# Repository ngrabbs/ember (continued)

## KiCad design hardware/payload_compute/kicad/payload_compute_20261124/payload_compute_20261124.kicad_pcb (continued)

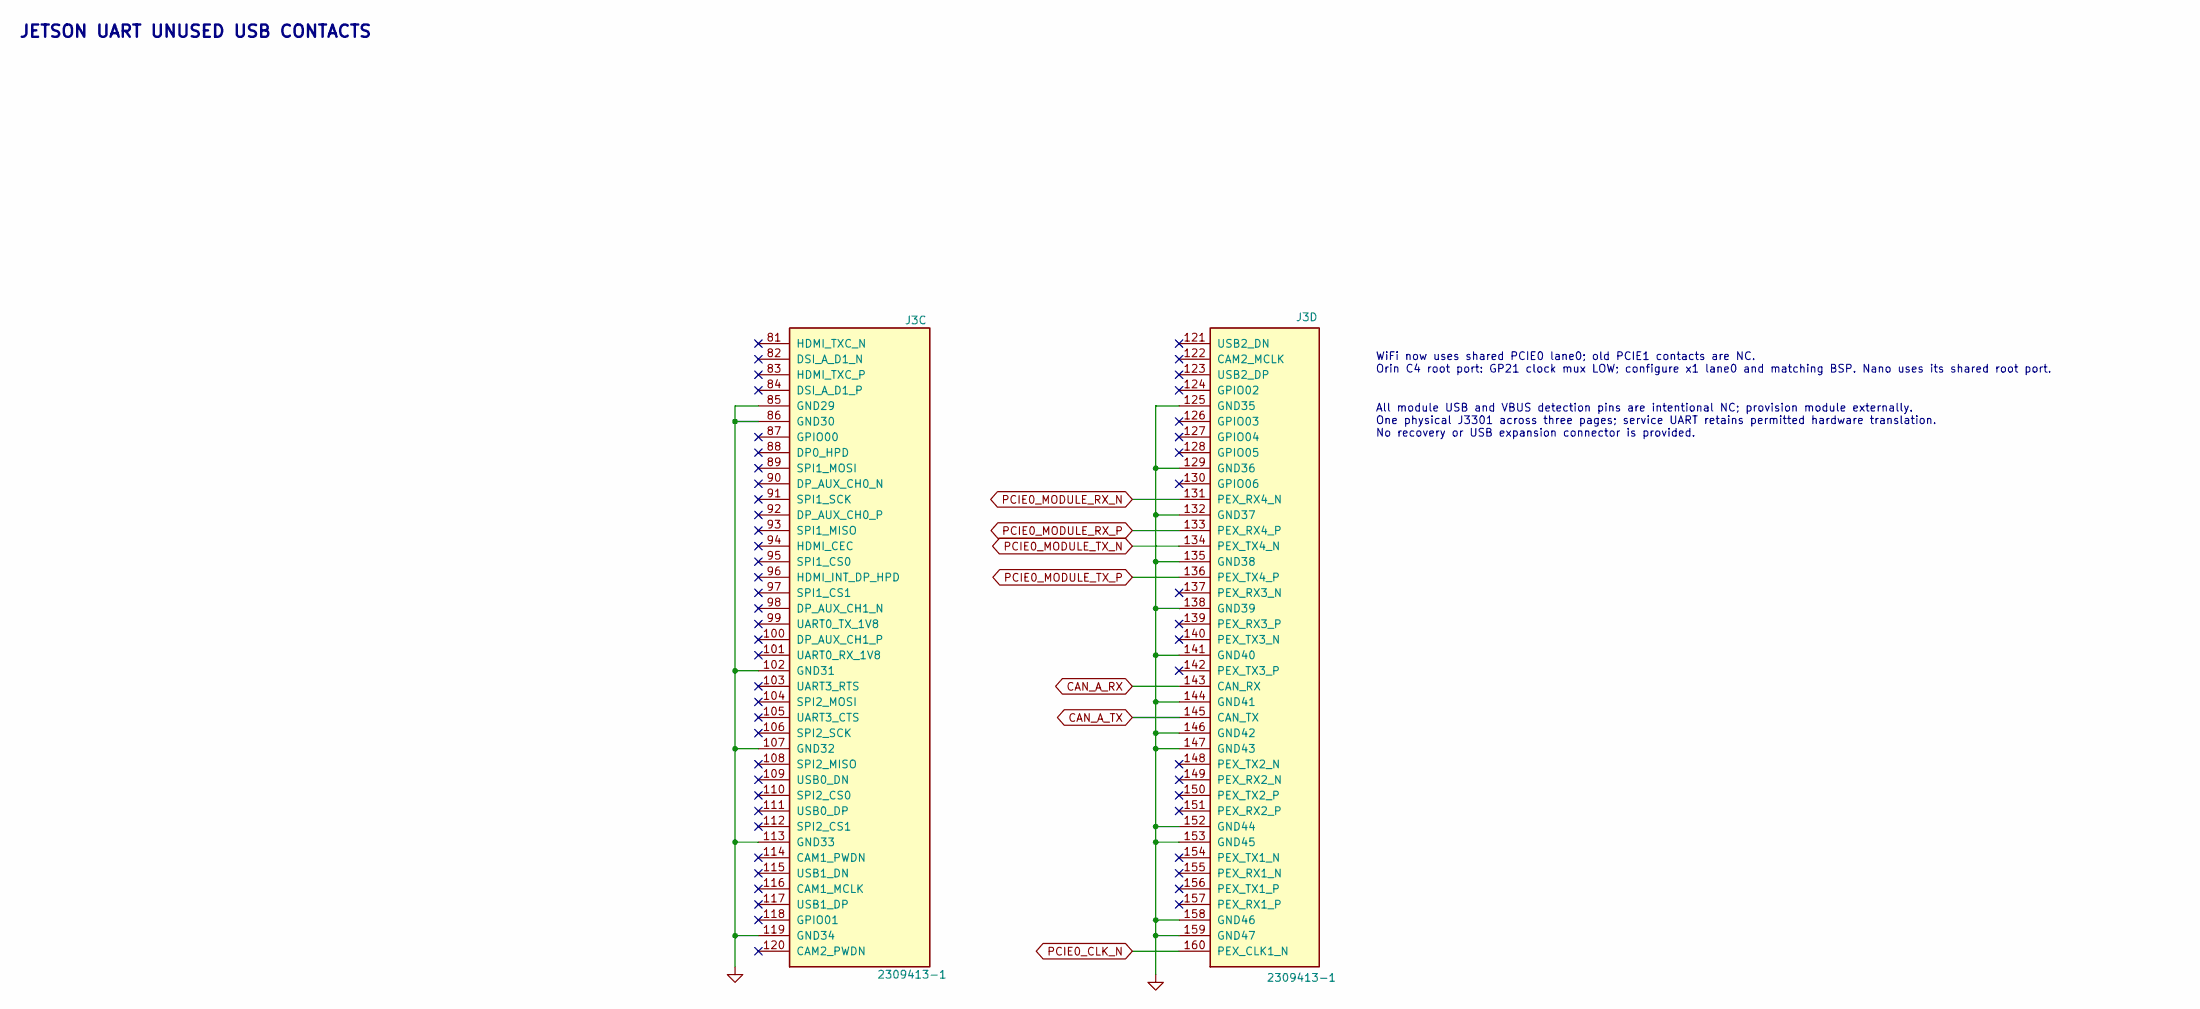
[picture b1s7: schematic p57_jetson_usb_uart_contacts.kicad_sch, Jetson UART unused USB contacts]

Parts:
J3: 2309413-1; TE_2309413_1; MPN 2309413-1

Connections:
CAN_A_RX: J3.143 (CAN_RX); also elsewhere on the board
CAN_A_TX: J3.145 (CAN_TX); also elsewhere on the board
GND: J3.85 (GND29), J3.86 (GND30), J3.102 (GND31), J3.107 (GND32), J3.113 (GND33), J3.119 (GND34), J3.125 (GND35), J3.129 (GND36), J3.132 (GND37), J3.135 (GND38), J3.138 (GND39), J3.141 (GND40), J3.144 (GND41), J3.146 (GND42), J3.147 (GND43), J3.152 (GND44), J3.153 (GND45), J3.158 (GND46), J3.159 (GND47); also elsewhere on the board
PCIE0_CLK_N: J3.160 (PEX_CLK1_N); also elsewhere on the board
PCIE0_MODULE_RX_N: J3.131 (PEX_RX4_N); also elsewhere on the board
PCIE0_MODULE_RX_P: J3.133 (PEX_RX4_P); also elsewhere on the board
PCIE0_MODULE_TX_N: J3.134 (PEX_TX4_N); also elsewhere on the board
PCIE0_MODULE_TX_P: J3.136 (PEX_TX4_P); also elsewhere on the board

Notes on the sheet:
JETSON UART UNUSED USB CONTACTS
All module USB and VBUS detection pins are intentional NC; provision module externally. One physical J3301 across three pages; service UART retains permitted hardware translation. No recovery or USB expansion connector is provided.
WiFi now uses shared PCIE0 lane0; old PCIE1 contacts are NC. Orin C4 root port: GP21 clock mux LOW; configure x1 lane0 and matching BSP. Nano uses its shared root port.

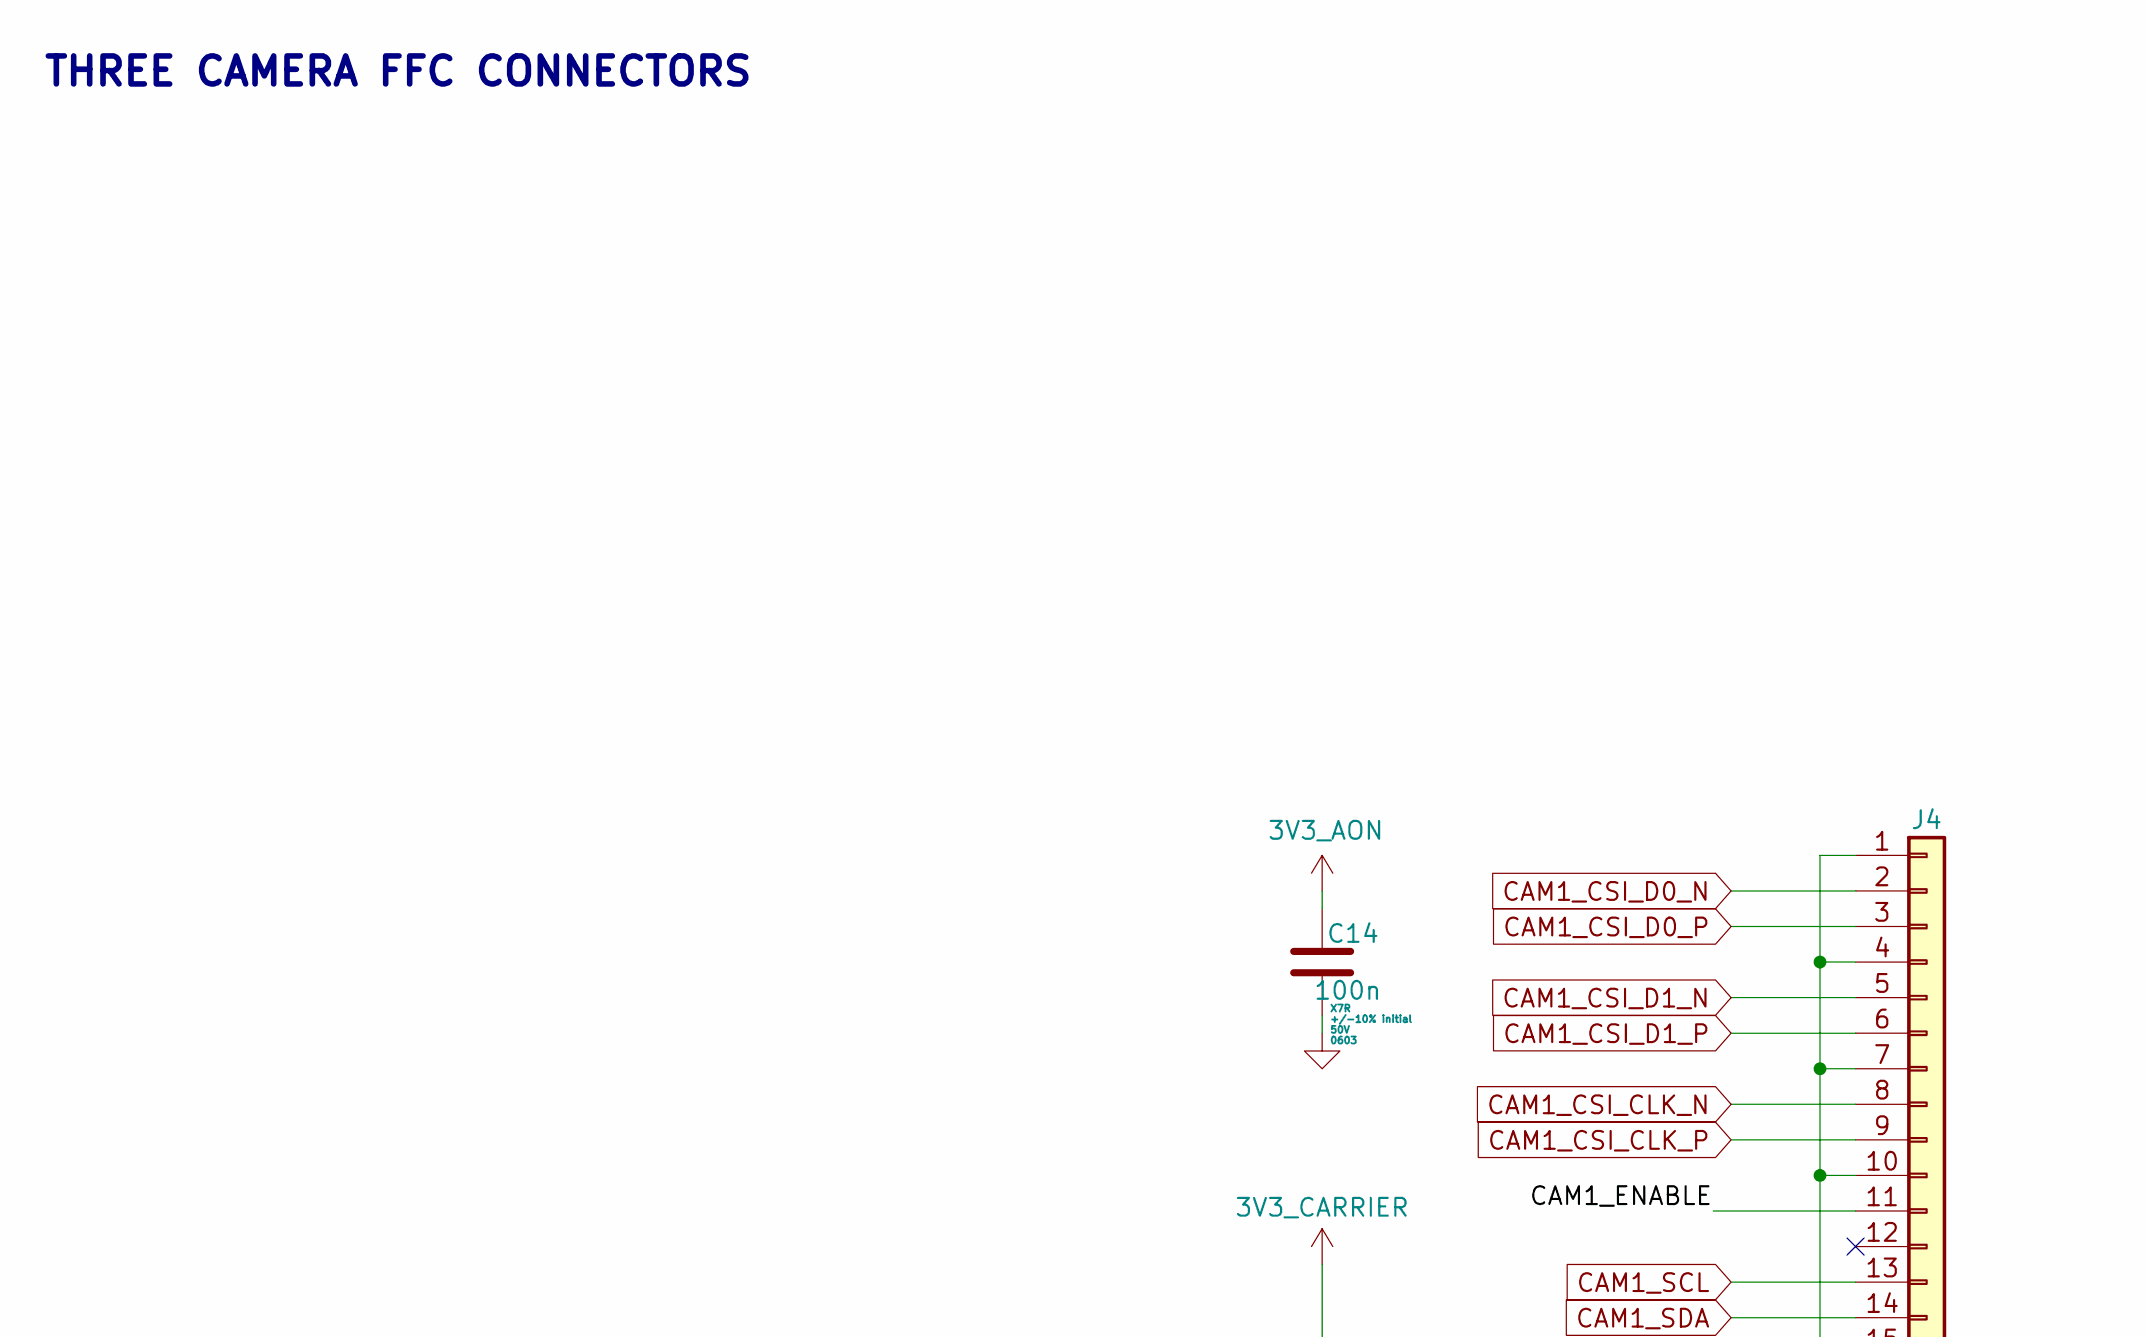
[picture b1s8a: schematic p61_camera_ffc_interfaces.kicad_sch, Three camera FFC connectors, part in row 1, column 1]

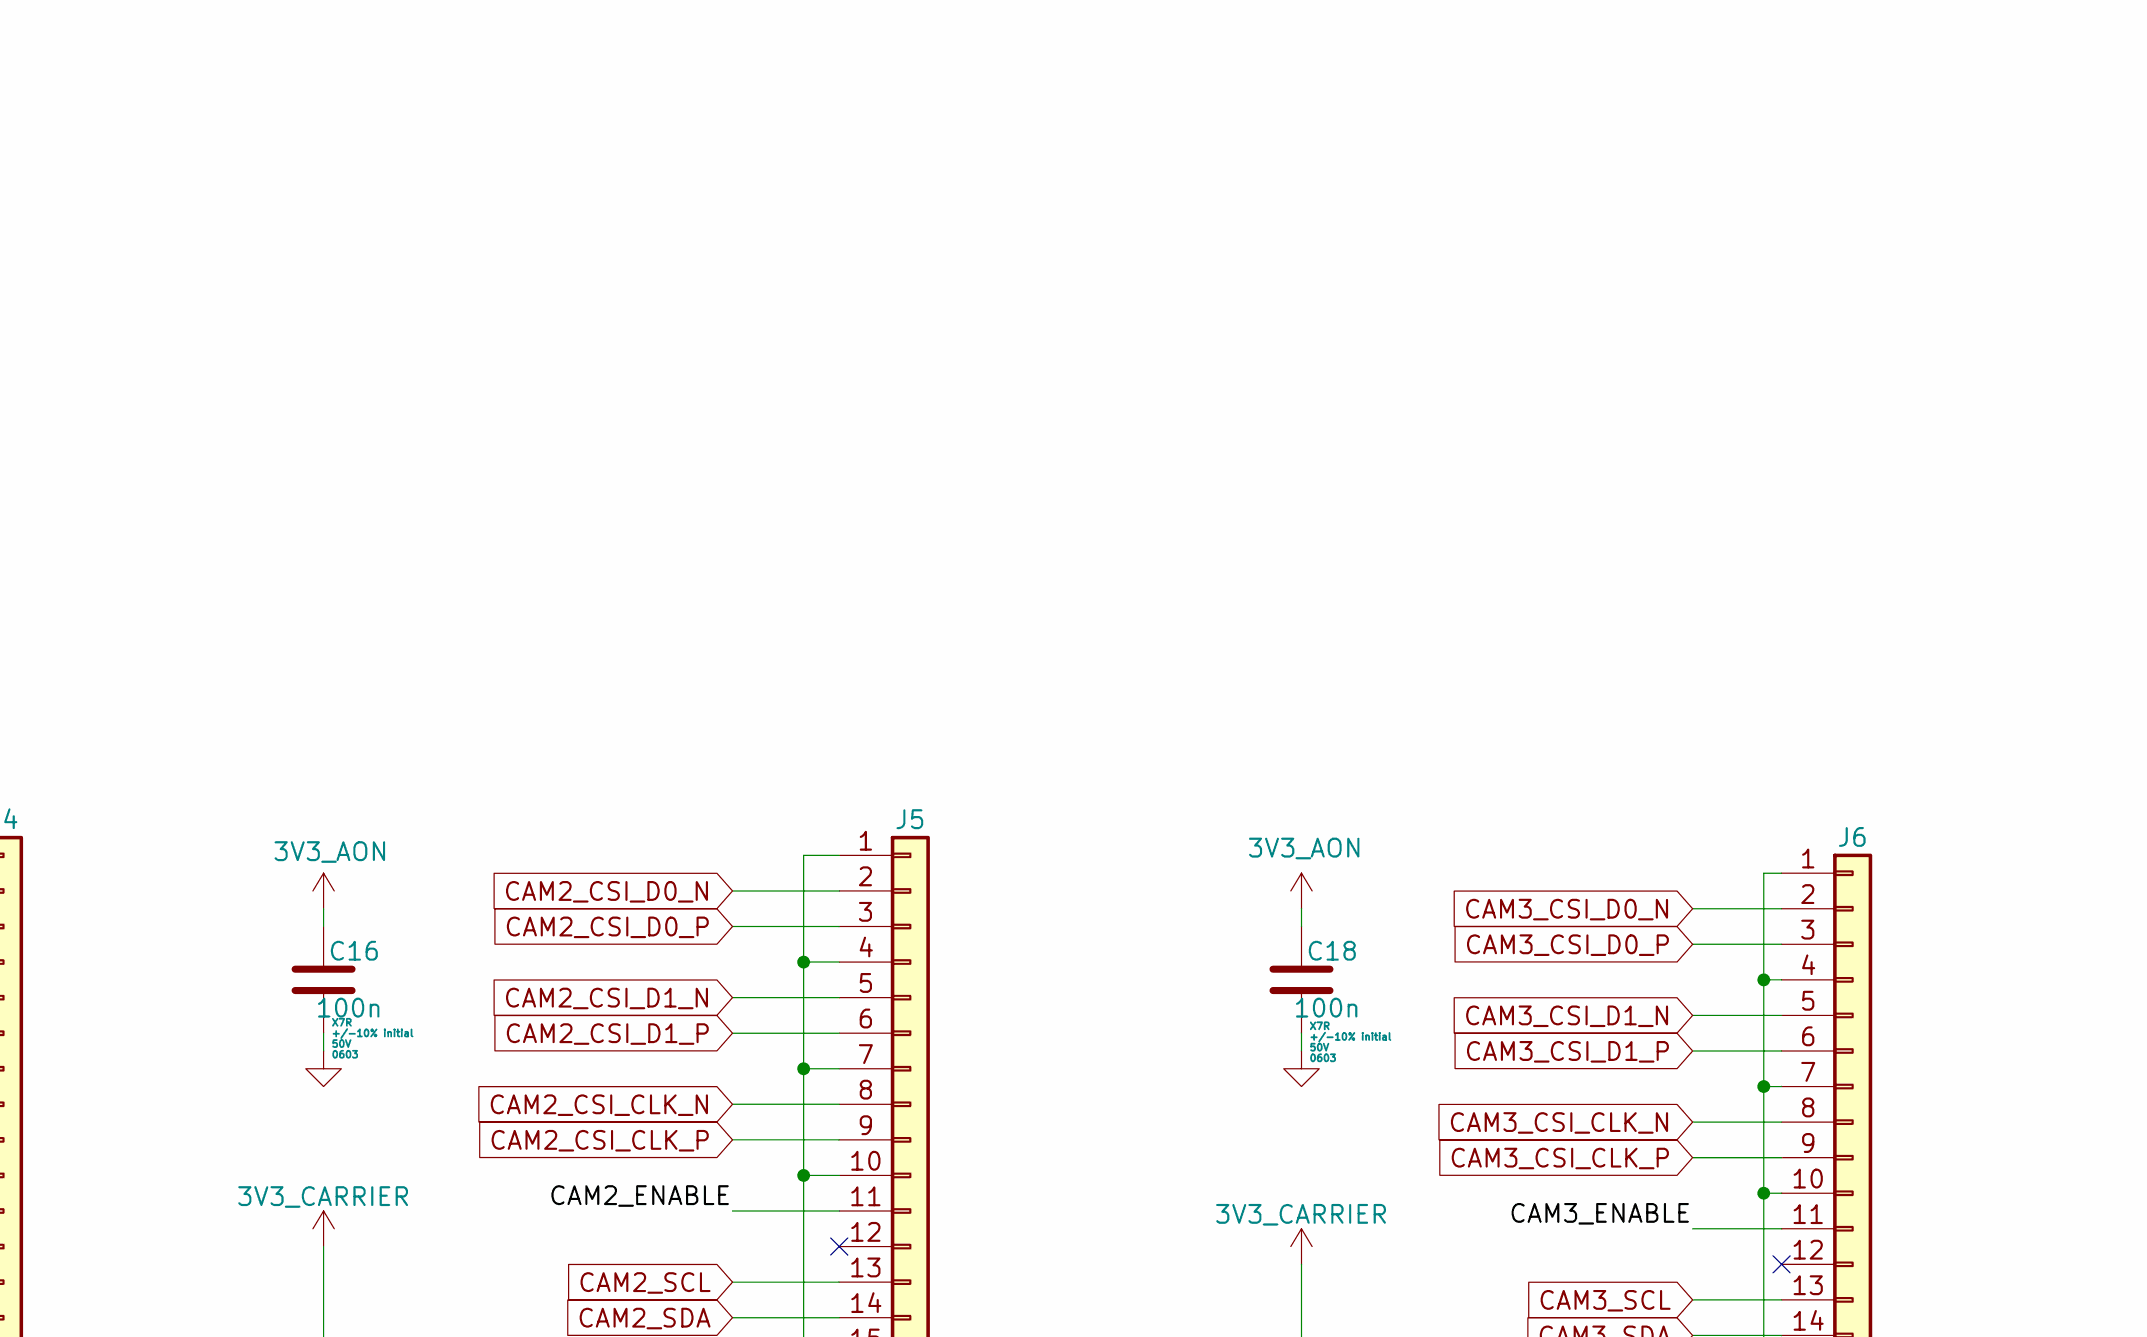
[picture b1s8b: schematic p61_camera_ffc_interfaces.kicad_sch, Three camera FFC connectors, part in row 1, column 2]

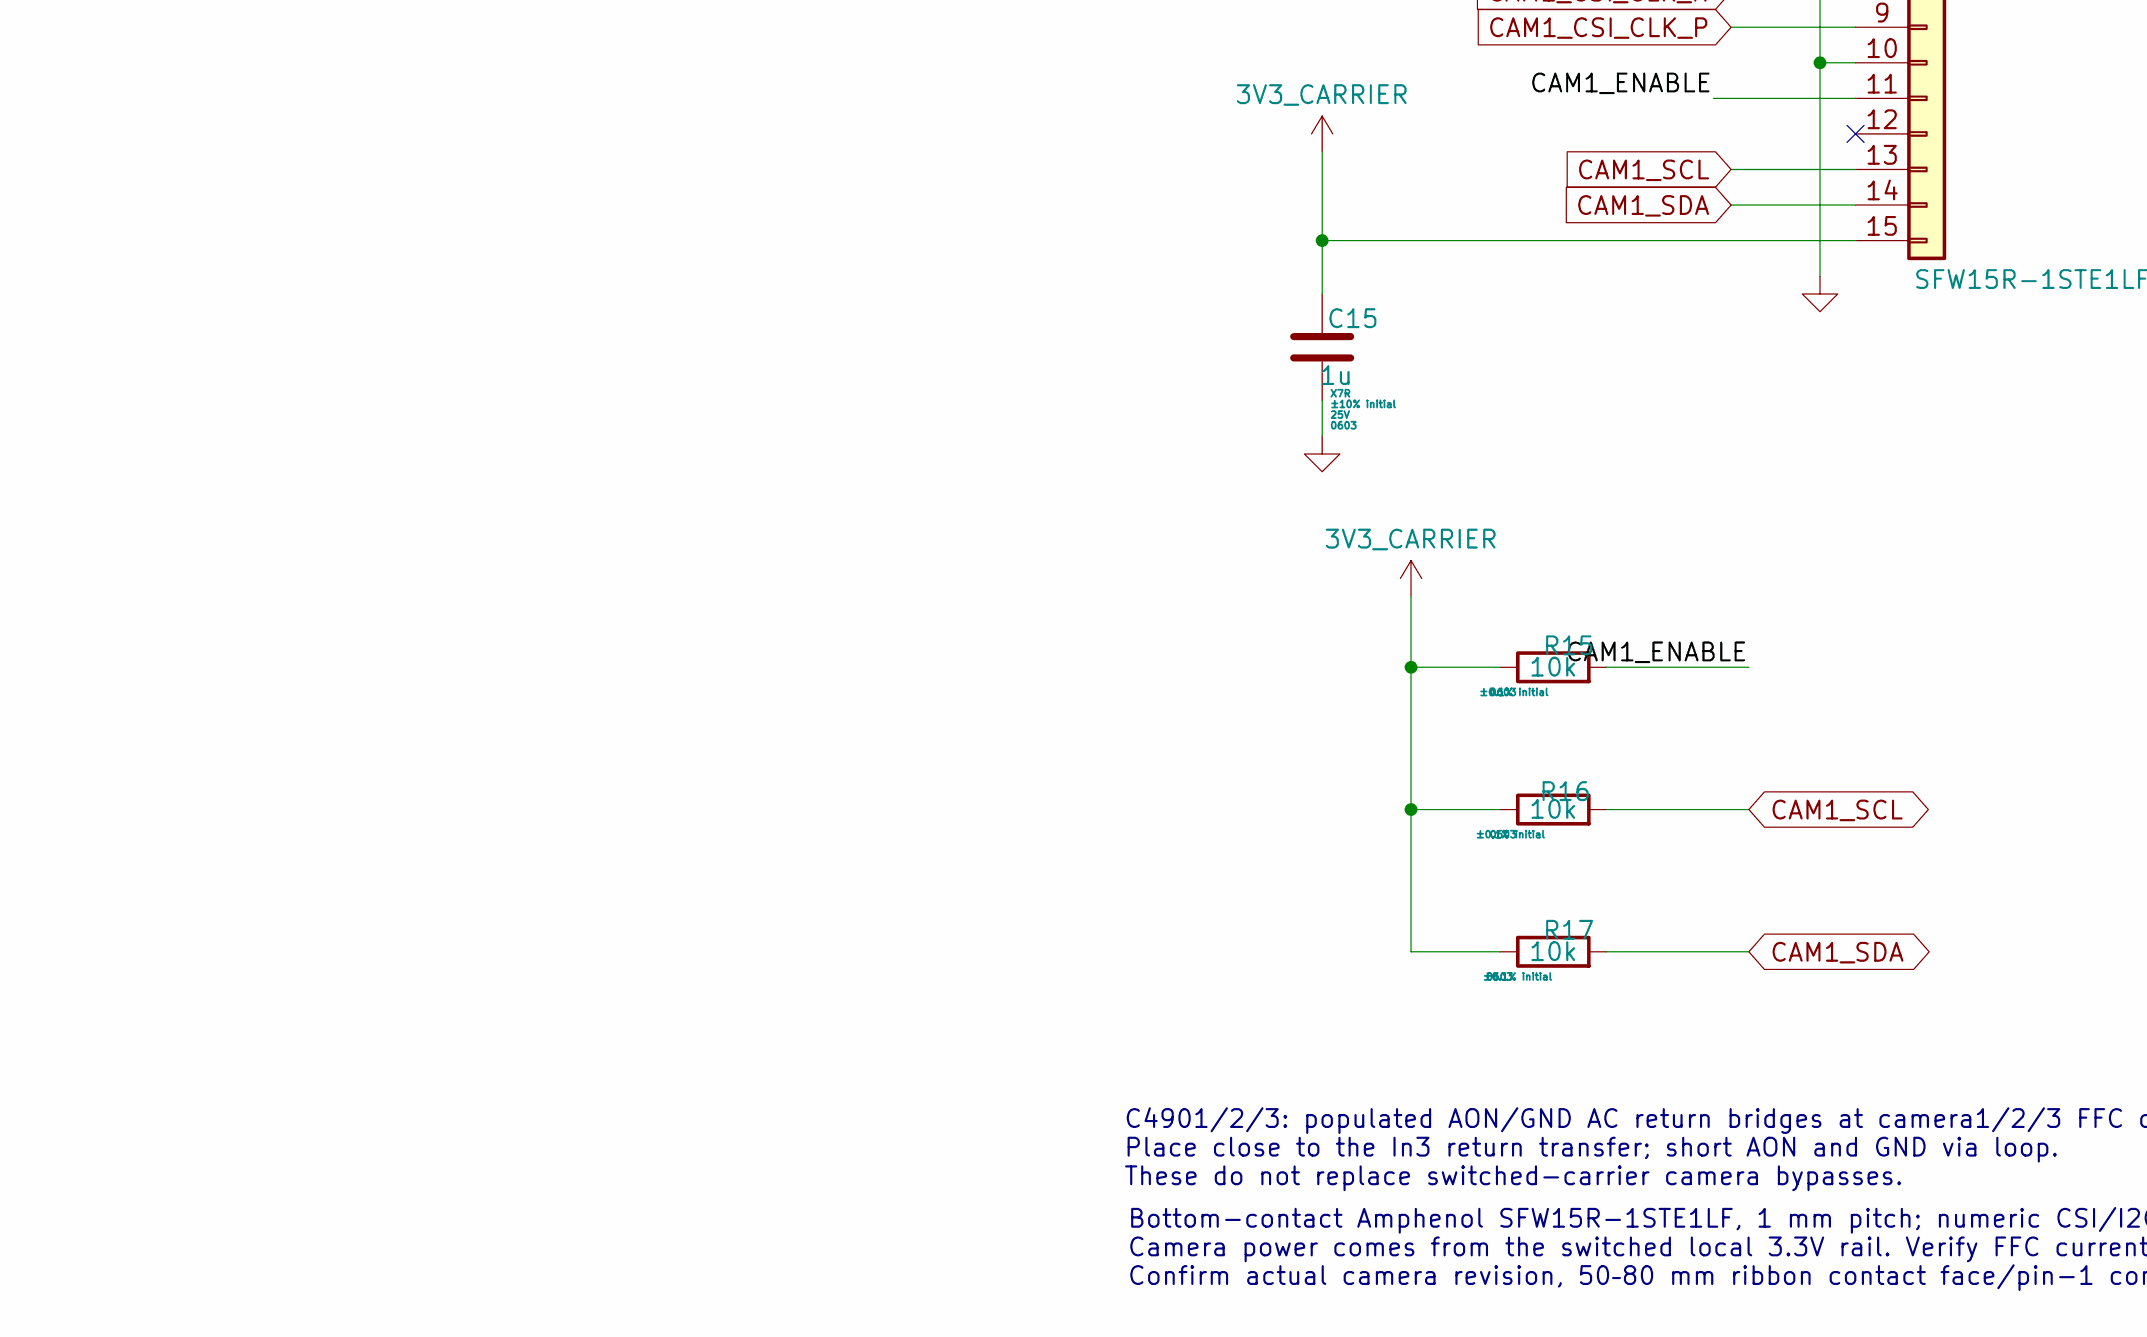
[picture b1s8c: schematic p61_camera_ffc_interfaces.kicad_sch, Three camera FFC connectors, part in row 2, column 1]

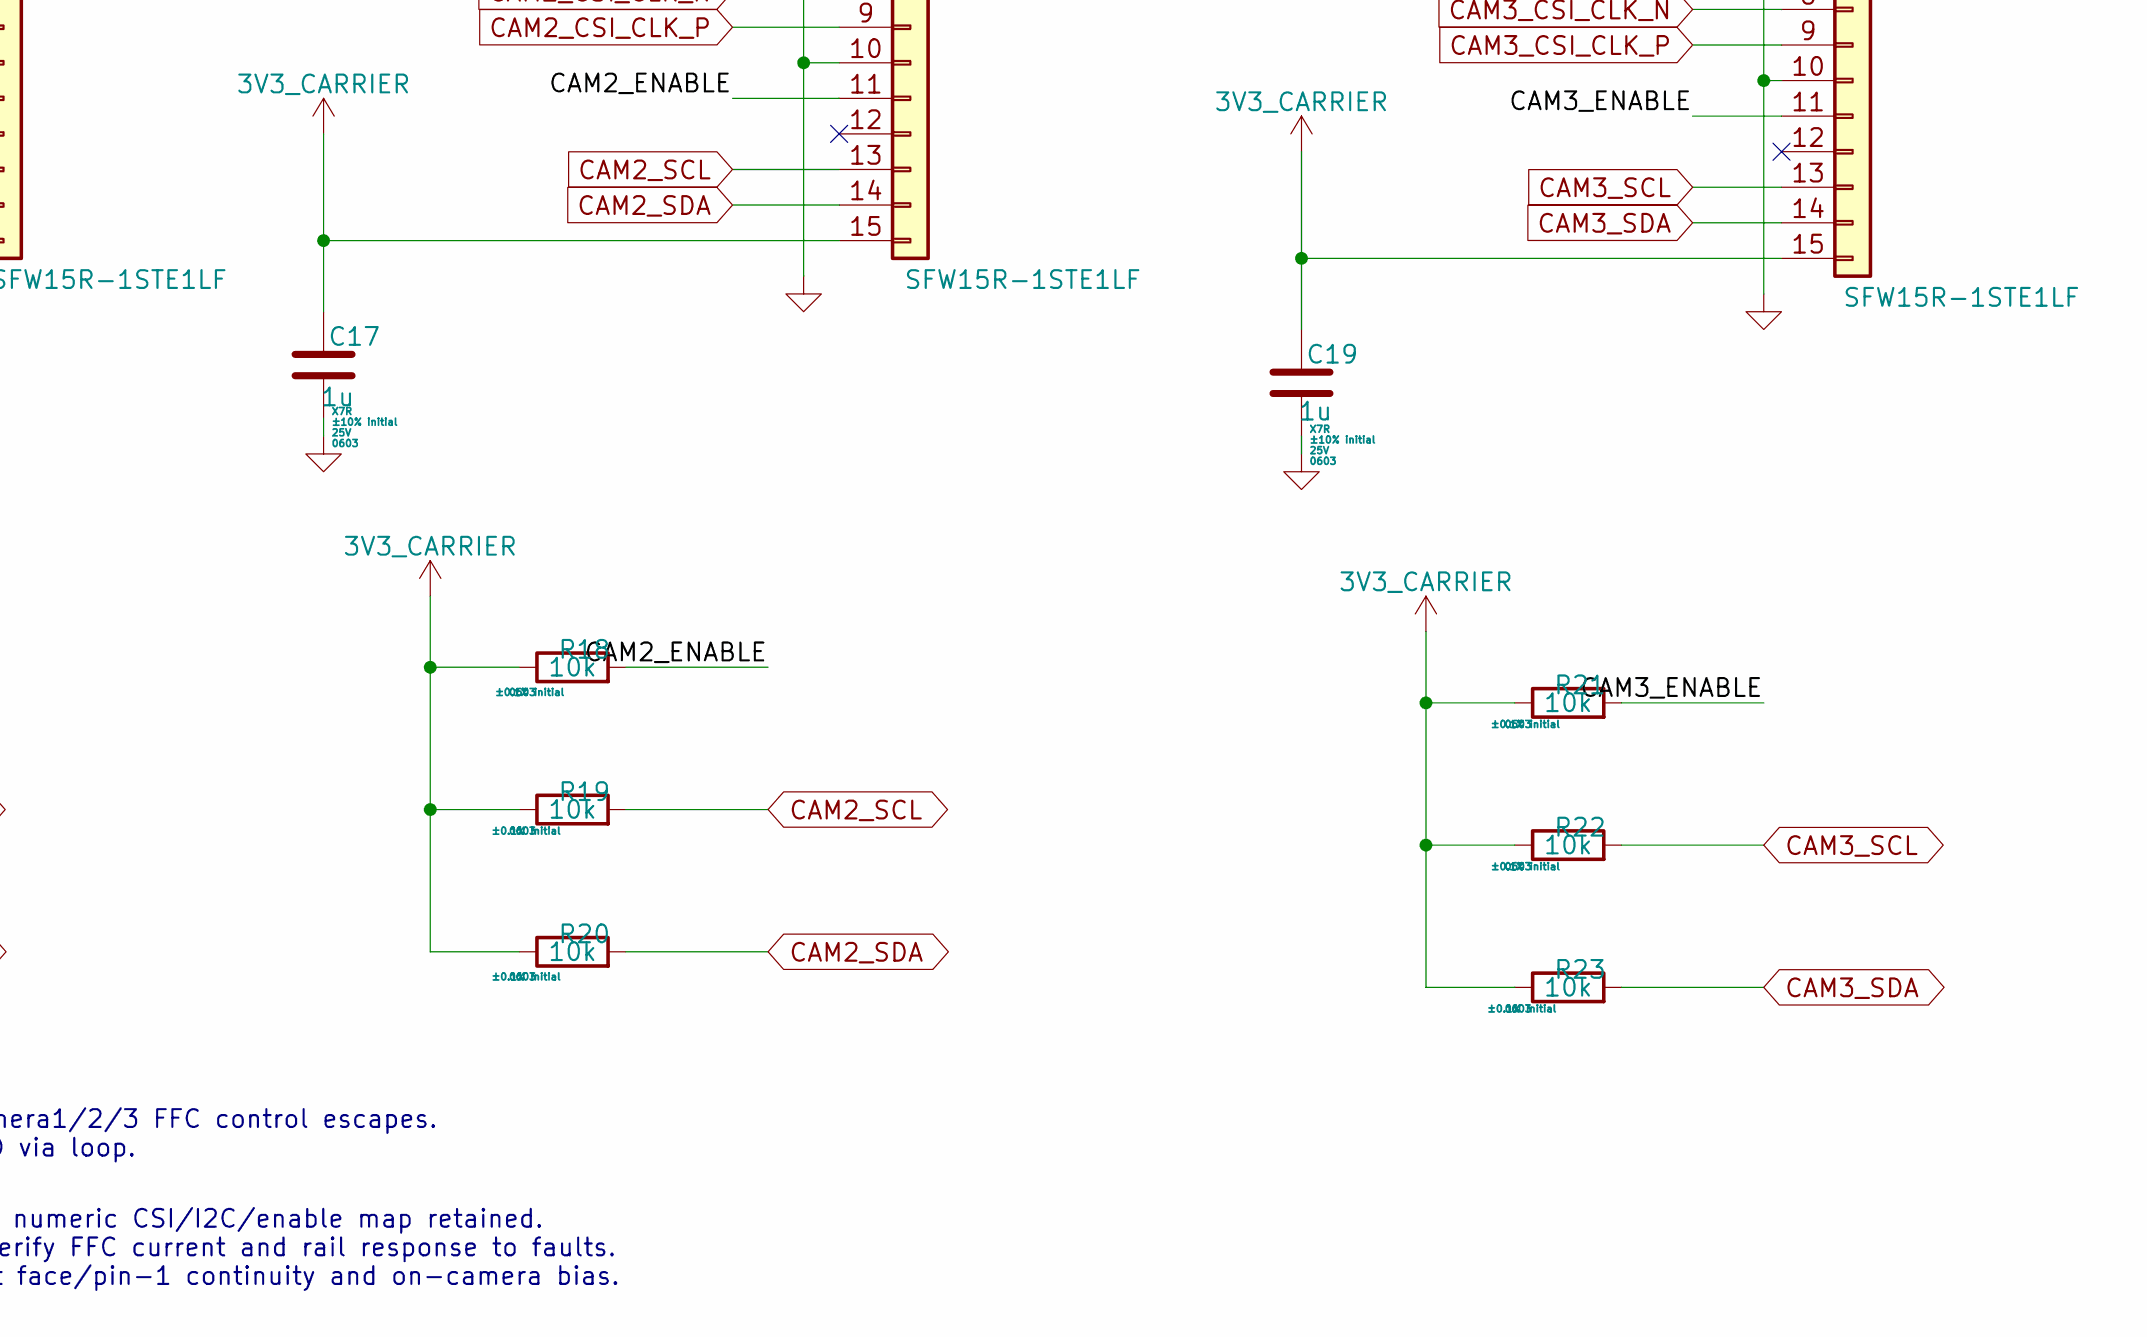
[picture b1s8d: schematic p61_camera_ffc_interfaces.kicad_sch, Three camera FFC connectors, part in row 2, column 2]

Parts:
C14, C16, C18: 100n; C_0603_1608Metric; Tolerance +/-10% initial; Voltage 50V; MFG P/N C0603C104K5RACTU
C15, C17, C19: 1u; C_0603_1608Metric; Tolerance +/-10% initial; Voltage 25V; MFG P/N C0603C105K3RACTU
J4, J5, J6: SFW15R-1STE1LF; Amphenol_SFW15R_1STE1LF_1mm_Bottom; MPN SFW15R-1STE1LF
R15, R16, R17, R18, R19, R20, R21, R22, R23: 10k; R_0603_1608Metric; Tolerance +/-0.1% initial; MFG P/N TNPW060310K0BEEA

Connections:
3V3_AON: C14.1, C16.1, C18.1; also elsewhere on the board
3V3_CARRIER: C15.1, C17.1, C19.1, J4.15, J5.15, J6.15, R15.1, R16.1, R17.1, R18.1, R19.1, R20.1, R21.1, R22.1, R23.1; also elsewhere on the board
/Three camera FFC connectors/CAM1_ENABLE: J4.11, R15.2
/Three camera FFC connectors/CAM2_ENABLE: J5.11, R18.2
/Three camera FFC connectors/CAM3_ENABLE: J6.11, R21.2
CAM1_CSI_CLK_N: J4.8; also elsewhere on the board
CAM1_CSI_CLK_P: J4.9; also elsewhere on the board
CAM1_CSI_D0_N: J4.2; also elsewhere on the board
CAM1_CSI_D0_P: J4.3; also elsewhere on the board
CAM1_CSI_D1_N: J4.5; also elsewhere on the board
CAM1_CSI_D1_P: J4.6; also elsewhere on the board
CAM1_SCL: J4.13, R16.2; also elsewhere on the board
CAM1_SDA: J4.14, R17.2; also elsewhere on the board
CAM2_CSI_CLK_N: J5.8; also elsewhere on the board
CAM2_CSI_CLK_P: J5.9; also elsewhere on the board
CAM2_CSI_D0_N: J5.2; also elsewhere on the board
CAM2_CSI_D0_P: J5.3; also elsewhere on the board
CAM2_CSI_D1_N: J5.5; also elsewhere on the board
CAM2_CSI_D1_P: J5.6; also elsewhere on the board
CAM2_SCL: J5.13, R19.2; also elsewhere on the board
CAM2_SDA: J5.14, R20.2; also elsewhere on the board
CAM3_CSI_CLK_N: J6.8; also elsewhere on the board
CAM3_CSI_CLK_P: J6.9; also elsewhere on the board
CAM3_CSI_D0_N: J6.2; also elsewhere on the board
CAM3_CSI_D0_P: J6.3; also elsewhere on the board
CAM3_CSI_D1_N: J6.5; also elsewhere on the board
CAM3_CSI_D1_P: J6.6; also elsewhere on the board
CAM3_SCL: J6.13, R22.2; also elsewhere on the board
CAM3_SDA: J6.14, R23.2; also elsewhere on the board
GND: C14.2, C15.2, C16.2, C17.2, C18.2, C19.2, J4.1, J4.4, J4.7, J4.10, J5.1, J5.4, J5.7, J5.10, J6.1, J6.4, J6.7, J6.10; also elsewhere on the board

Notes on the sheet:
Bottom-contact Amphenol SFW15R-1STE1LF, 1 mm pitch; numeric CSI/I2C/enable map retained. Camera power comes from the switched local 3.3V rail. Verify FFC current and rail response to faults. Confirm actual camera revision, 50–80 mm ribbon contact face/pin-1 continuity and on-camera bias.
C4901/2/3: populated AON/GND AC return bridges at camera1/2/3 FFC control escapes. Place close to the In3 return transfer; short AON and GND via loop. These do not replace switched-carrier camera bypasses.
THREE CAMERA FFC CONNECTORS

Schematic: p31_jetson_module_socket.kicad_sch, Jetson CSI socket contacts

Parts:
J3: 2309413-1; TE_2309413_1; MPN 2309413-1

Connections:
CAM1_CSI_CLK_N: J3.10 (CSI_A_CLK_N); also elsewhere on the board
CAM1_CSI_CLK_P: J3.12 (CSI_A_CLK_P); also elsewhere on the board
CAM1_CSI_D0_N: J3.4 (CSI_A_D0_N); also elsewhere on the board
CAM1_CSI_D0_P: J3.6 (CSI_A_D0_P); also elsewhere on the board
CAM1_CSI_D1_N: J3.16 (CSI_A_D1_N); also elsewhere on the board
CAM1_CSI_D1_P: J3.18 (CSI_A_D1_P); also elsewhere on the board
CAM2_CSI_CLK_N: J3.27 (CSI_F_CLK_N); also elsewhere on the board
CAM2_CSI_CLK_P: J3.29 (CSI_F_CLK_P); also elsewhere on the board
CAM2_CSI_D0_N: J3.21 (CSI_F_D0_N); also elsewhere on the board
CAM2_CSI_D0_P: J3.23 (CSI_F_D0_P); also elsewhere on the board
CAM2_CSI_D1_N: J3.33 (CSI_F_D1_N); also elsewhere on the board
CAM2_CSI_D1_P: J3.35 (CSI_F_D1_P); also elsewhere on the board
CAM3_CSI_CLK_N: J3.28 (CSI_E_CLK_N); also elsewhere on the board
CAM3_CSI_CLK_P: J3.30 (CSI_E_CLK_P); also elsewhere on the board
CAM3_CSI_D0_N: J3.22 (CSI_E_D0_N); also elsewhere on the board
CAM3_CSI_D0_P: J3.24 (CSI_E_D0_P); also elsewhere on the board
CAM3_CSI_D1_N: J3.34 (CSI_E_D1_N); also elsewhere on the board
CAM3_CSI_D1_P: J3.36 (CSI_E_D1_P); also elsewhere on the board
GND: J3.1 (GND1), J3.2 (GND2), J3.7 (GND3), J3.8 (GND4), J3.13 (GND5), J3.14 (GND6), J3.19 (GND7), J3.20 (GND8), J3.25 (GND9), J3.26 (GND10), J3.31 (GND11), J3.32 (GND12), J3.37 (GND13), J3.38 (GND14), J3.43 (GND15), J3.44 (GND16), J3.49 (GND17), J3.50 (GND18), J3.55 (GND19), J3.56 (GND20), J3.61 (GND21), J3.62 (GND22), J3.67 (GND23), J3.68 (GND24), J3.73 (GND25), J3.74 (GND26), J3.79 (GND27), J3.80 (GND28); also elsewhere on the board

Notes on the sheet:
JETSON CSI SOCKET CONTACTS

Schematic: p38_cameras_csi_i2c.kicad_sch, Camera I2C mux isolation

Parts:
C25, C26, C27, C28: 100n; C_0603_1608Metric; Tolerance +/-10% initial; Voltage 50V; MFG P/N C0603C104K5RACTU
R26, R27: 10k; R_0603_1608Metric; Tolerance +/-0.1% initial; MFG P/N TNPW060310K0BEEA
U9: TMUX1511PWR; TSSOP-14_4.4x5mm_P0.65mm; MFG P/N TMUX1511PWR
U10: TCA9546APWR; TSSOP-16_4.4x5mm_P0.65mm; MPN TCA9546APWR
U11: SN74LVC1G125DBVR; TI_DBV0005A_SOT23_5; MPN SN74LVC1G125DBVR

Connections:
3V3_AON: C25.1, C26.1, U9.14 (VDD); also elsewhere on the board
3V3_CARRIER: C27.1, C28.1, R27.1, U10.16 (VCC), U11.5 (VCC); also elsewhere on the board
/Camera I2C mux isolation/CAM_I2C_SCL_ISO: U9.6 (D2), U10.14 (SCL)
/Camera I2C mux isolation/CAM_I2C_SDA_ISO: U9.3 (D1), U10.15 (SDA)
/Camera I2C mux isolation/CAM_MUX_RESET_N: R27.2, U10.3 (~RESET), U11.4
CAM1_SCL: U10.5 (SC0); also elsewhere on the board
CAM1_SDA: U10.4 (SD0); also elsewhere on the board
CAM2_SCL: U10.7 (SC1); also elsewhere on the board
CAM2_SDA: U10.6 (SD1); also elsewhere on the board
CAM3_SCL: U10.10 (SC2); also elsewhere on the board
CAM3_SDA: U10.9 (SD2); also elsewhere on the board
CAM_I2C_SCL: U9.5 (S2); also elsewhere on the board
CAM_I2C_SDA: U9.2 (S1); also elsewhere on the board
CARRIER_IO_PERMISSION_AON: R26.1, U9.1 (SEL1), U9.4 (SEL2), U11.2; also elsewhere on the board
GND: C25.2, C26.2, C27.2, C28.2, R26.2, U9.7 (GND), U9.8 (D3), U9.9 (S3), U9.10 (SEL3), U9.11 (D4), U9.12 (S4), U9.13 (SEL4), U10.1 (A0), U10.2 (A1), U10.8 (GND), U10.13 (A2), U11.1, U11.3 (GND); also elsewhere on the board

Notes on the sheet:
CAMERA I2C MUX ISOLATION

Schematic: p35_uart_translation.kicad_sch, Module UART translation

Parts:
C29, C30, C31: 100n; C_0603_1608Metric; Tolerance +/-10% initial; Voltage 50V; MFG P/N C0603C104K5RACTU
R28: 100k; R_0603_1608Metric; Tolerance +/-0.1% initial; MFG P/N TNPW0603100KBEEA
TP1: GND; TestPoint_Pad_D1.0mm; MFG P/N PCB_TEST_PAD_1MM
TP2: CONSOLE_HOST_RX_3V3; TestPoint_Pad_D1.0mm; MFG P/N PCB_TEST_PAD_1MM
TP3: CONSOLE_HOST_TX_3V3; TestPoint_Pad_D1.0mm; MFG P/N PCB_TEST_PAD_1MM
U12: SN74AXC2T245RSWR; TI_RSW0010A_AXC; MPN SN74AXC2T245RSWR
U13: SN74LVC1G14DBVR; TI_DBV0005A_SOT23_5; MFG P/N SN74LVC1G14DBVR

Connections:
1V8_CARRIER: C30.1, U12.6 (VCCB); also elsewhere on the board
3V3_AON: C29.1, C31.1, R28.1, U12.7 (VCCA), U12.10 (DIR1), U13.5 (VCC); also elsewhere on the board
/Module UART translation/CONSOLE_HOST_RX_3V3: TP2.1 (1_1), U12.9 (A2)
/Module UART translation/CONSOLE_HOST_TX_3V3: TP3.1 (1_1), U12.8 (A1)
/Module UART translation/UART_OE_N: R28.2, U12.2 (OE_N), U13.4
CARRIER_IO_PERMISSION_AON: U13.2; also elsewhere on the board
GND: C29.2, C30.2, C31.2, TP1.1 (1_1), U12.1 (DIR2), U12.3 (GND), U13.3 (GND); also elsewhere on the board
JETSON_CONSOLE_RX_1V8: U12.5 (B1); also elsewhere on the board
JETSON_CONSOLE_TX_1V8: U12.4 (B2); also elsewhere on the board

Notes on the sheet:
MODULE UART TRANSLATION

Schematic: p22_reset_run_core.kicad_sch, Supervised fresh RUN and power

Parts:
C32, C34, C35, C36, C37: 100n; C_0603_1608Metric; Tolerance +/-10% initial; Voltage 50V; MFG P/N C0603C104K5RACTU
C33: 1u; C_0603_1608Metric; Tolerance +/-10% initial; Voltage 25V; MFG P/N C0603C105K3RACTU
D1: 1N4148WS; D_SOD-323; MFG P/N 1N4148WS
R29, R32: 10k; R_0603_1608Metric; Tolerance +/-0.1% initial; MFG P/N TNPW060310K0BEEA
R30: 100k; R_0603_1608Metric; Tolerance +/-0.1% initial; MFG P/N TNPW0603100KBEEA
R31: 1k; R_0603_1608Metric; Tolerance +/-0.1% initial; MFG P/N TNPW06031K00BEEA
U4: SN74LVC3G17DCUR; VSSOP-8_2.3x2mm_P0.5mm; MFG P/N SN74LVC3G17DCUR
U14: TPS3808G33DBVR; TI_DBV0006A_SOT23_6; MFG P/N TPS3808G33DBVR
U15, U16: SN74LVC1G11DBVR; TI_DBV0006A_SOT23_6; MFG P/N SN74LVC1G11DBVR
U17: SN74LVC1G74DCUR; TI_DCU0008A_VSSOP_8; MFG P/N SN74LVC1G74DCUR

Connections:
3V3_AON: C32.1, C34.1, C35.1, C36.1, C37.1, R29.1, U4.8 (VCC), U14.3 (MR_N), U14.5 (SENSE), U14.6 (VDD), U15.5 (VCC), U16.5 (VCC), U17.2 (D), U17.7 (PRE_N), U17.8 (VCC); also elsewhere on the board
/Module electrical auto-on and shutdown/AON_POR_N: R29.2, U14.1 (RESET_N), U15.6, U16.6
/Module electrical auto-on and shutdown/MODULE_CLEAR_N: U15.4, U17.6 (CLR_N)
/Module electrical auto-on and shutdown/MODULE_START_CLK: U4.2, U17.1 (CLK)
GND: C32.2, C33.2, C34.2, C35.2, C36.2, C37.2, R32.2, U4.4 (GND), U14.2 (GND), U15.2 (GND), U16.2 (GND), U17.4 (GND); also elsewhere on the board
MAIN_BUCK_PG_AON: U15.1, U16.1, U16.3; also elsewhere on the board
MODULE_POWER_REQUEST: R32.1, U17.5 (Q); also elsewhere on the board
unnamed: C33.1, D1.2 (A), R30.2, U4.6
unnamed: D1.1 (K), R31.2
unnamed: R30.1, R31.1, U16.4
SHUTDOWN_OK_AON: U15.3; also elsewhere on the board

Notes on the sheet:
JETSON AUTO-ON AND CAN-INITIATED SHUTDOWN EPS applies VBAT. Valid supplies and the RC delay clock U105 to assert POWER_EN. IHU requests Linux shutdown over CAN. Jetson SHUTDOWN_REQ clears U105 and drops POWER_EN. Releasing SHUTDOWN_REQ alone does not restart the module. Cycle EPS VBAT for a normal 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

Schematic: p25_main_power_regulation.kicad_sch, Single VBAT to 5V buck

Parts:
C39, C42: 10u; TDK_C3225_Recommended; Tolerance +/-10%; Voltage 50V; MPN C3225X7R1H106K250AC
C40, C41, C45, C53: 100n; C_0805_2012Metric; Tolerance +/-10% initial; Voltage 50V; MFG P/N C0805C104K5RACTU
C44: 2.2u; C_0805_2012Metric; Tolerance +/-10% initial; Voltage 25V; MFG P/N C0805C225K3RACTU
C46, C47, C48, C49, C50, C52, C55, C56: 47u; C_1210_3225Metric; Tolerance +/-10%; Voltage 10V; MPN GRM32ER71A476KE15L
C51: 150p DNP; C_0805_2012Metric; Tolerance +/-5% initial; Voltage 50V; MFG P/N C0805C151J5GACTU; not fitted
L2: 4.7u; L_Coilcraft_XAL7070-XXX; Tolerance +/-20%; MPN XAL7070-472MEC
R33: 24.3k; R_0603_1608Metric; Tolerance +/-0.1% initial; MFG P/N TNPW060324K3BEEA
R34: 412k LOW3A 4pF 4ms; R_0603_1608Metric; Tolerance +/-0.01% initial; MFG P/N P0603C4123LNT
R35: 0; Panasonic_ERJ3G_Recommended; Tolerance N/A — jumper; Rmax50mOhm; MFG P/N ERJ3GEY0R00V
R36, R37: 10; R_0603_1608Metric; Tolerance +/-0.1% initial; MFG P/N TNPW060310R0BEEA
R38, R39: 2.2; R_0603_1608Metric; Tolerance +/-0.5% initial; MFG P/N TNPW06032R20DEEA
R40: 9.10k; R_0603_1608Metric; Tolerance +/-0.01% initial; MPN P0603C9101LNT
R41: 1.00k; R_0603_1608Metric; Tolerance +/-0.01% initial; MPN P0603C1001LNT
U18: TPS543620RPYR; TI_RPY0014A_Prototype; MPN TPS543620RPYR

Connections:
5V0_MODULE: C46.1, C47.1, C48.1, C49.1, C50.1, C51.2, C52.1, C53.1, C55.1, C56.1, L2.2, R40.1; also elsewhere on the board
/Single VBAT to 5V buck/BUCK_FSEL: R33.1, U18.1 (SYNC_FSEL)
/Single VBAT to 5V buck/BUCK_MODE: R34.1, U18.2 (MODE)
GND: C39.2, C40.2, C41.2, C42.2, C44.2, C46.2, C47.2, C48.2, C49.2, C50.2, C52.2, C53.2, C55.2, C56.2, R33.2, R34.2, R39.2, U18.5 (AGND), U18.9 (PGND), U18.11 (PGND); also elsewhere on the board
MAIN5V_PG_RAW: U18.3 (PGOOD); also elsewhere on the board
MAIN_STACK_IN_POS: C39.1, C40.1, C41.1, C42.1, U18.8 (VIN), U18.12 (VIN); also elsewhere on the board
unnamed: C45.1, R35.2
unnamed: C45.2, L2.1, U18.10 (SW), U18.13 (SW)
unnamed: R36.1, R41.2
unnamed: R36.2, R37.1
unnamed: R37.2, R38.1
unnamed: R38.2, R39.1
unnamed: R35.1, U18.14 (BOOT)
unnamed: C44.1, U18.6 (BP5)
unnamed: C51.1, R40.2, R41.1, U18.4 (FB)

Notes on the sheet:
SIMPLIFIED: EN intentionally open, using internal enable pullup (TI TPS543620 SLUSDR5C section7.3.2). External managed VBAT controls power. No MCU request gate or EN divider. Input/output and inrush budgets remain held.
SINGLE VBAT TO 5V BUCK
9 x 47u bank: allocated effective C169.08u; step2.128A, Eq10 C150.55u at450kHz/50mV. Feedback9.10k/(1k+10+10+2.2+2.2): nominal4.9416V; precision R2403/4 TOTAL0.15%, small R TOTAL1%. Module7W+20%, fan0.36A; whole transient60mV allocated. Actual bias/ESR/loop/startup need measurement.

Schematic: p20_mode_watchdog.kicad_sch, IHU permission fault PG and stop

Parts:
R42: 10k; R_0603_1608Metric; Tolerance +/-0.1% initial; MFG P/N TNPW060310K0BEEA
R43: 100k; R_0603_1608Metric; Tolerance +/-0.1% initial; MFG P/N TNPW0603100KBEEA
U4: SN74LVC3G17DCUR; VSSOP-8_2.3x2mm_P0.5mm; MFG P/N SN74LVC3G17DCUR

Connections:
5V0_MODULE: R42.1; also elsewhere on the board
GND: R43.2; also elsewhere on the board
MAIN5V_PG_RAW: R42.2, R43.1, U4.1; also elsewhere on the board
MAIN_BUCK_PG_AON: U4.7; also elsewhere on the board

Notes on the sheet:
PHYSICAL MAIN5V POWER-GOOD RECEIVER 5V-sourced pullup falls with module supply;3.3V buffer is5V-input tolerant. No H1.50 permission receiver, PAYLOAD_FAULT output, stop-button or MCU status chain.

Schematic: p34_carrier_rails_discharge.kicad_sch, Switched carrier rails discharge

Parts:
C57: 1u; C_0603_1608Metric; Tolerance +/-10% initial; Voltage 25V; MFG P/N C0603C105K3RACTU
C58: 22n; C_0603_1608Metric; Tolerance +/-10% initial; Voltage 50V; MFG P/N C0603C223K5RACTU
C59, C61: 2.2u; C_0603_1608Metric; Tolerance +/-10% initial; Voltage 10V; MFG P/N C0603C225K8RACTU
C60: 10u; C_0805_2012Metric; Tolerance +/-10% initial; Voltage 10V; MFG P/N C0805C106K8RACTU
C62: 100n; C_0603_1608Metric; Tolerance +/-10% initial; Voltage 50V; MFG P/N C0603C104K5RACTU
Q1, Q2: PMV20XNE,115; SOT-23; MFG P/N PMV20XNE,115
R44, R47, R48: 10k; R_0603_1608Metric; Tolerance +/-0.1% initial; MFG P/N TNPW060310K0BEEA
R45, R46: 100; R_0603_1608Metric; Tolerance +/-0.1% initial; MFG P/N TNPW0603100RBEEA
R49: 1.5; R_2512_6332Metric; Tolerance +/-1%; MPN CRCW25121R50FKEGHP
R50: 10; R_2512_6332Metric; Tolerance +/-1%; MPN CRCW251210R0FKEGHP
U19: TPS22990DMLR; TI_DML0010A_WSON10; MFG P/N TPS22990DMLR
U20: TPS7A2018PDBVR; TI_DBV0005A_SOT23_5; MFG P/N TPS7A2018PDBVR
U21: SN74LVC1G14DBVR; TI_DBV0005A_SOT23_5; MFG P/N SN74LVC1G14DBVR

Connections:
1V8_CARRIER: C61.1, R50.1, U20.5 (OUT); also elsewhere on the board
3V3_AON: C57.1, C59.1, C62.1, U19.3 (VIN), U19.4 (VBIAS), U19.11 (VIN_EP), U20.1 (IN), U21.5 (VCC); also elsewhere on the board
3V3_CARRIER: C60.1, R49.1, U19.8 (VOUT), U19.9 (VOUT), U19.10 (VOUT); also elsewhere on the board
CARRIER_IO_PERMISSION_AON: R44.1, U19.5 (ON), U20.3 (EN), U21.2; also elsewhere on the board
GND: C57.2, C58.2, C59.2, C60.2, C61.2, C62.2, Q1.2 (S), Q2.2 (S), R44.2, R47.2, R48.2, U19.6 (GND), U19.7 (PG), U20.2 (GND), U21.3 (GND); also elsewhere on the board
unnamed: Q1.3 (D), R49.2
unnamed: Q1.1 (G), R45.2, R47.1
unnamed: Q2.3 (D), R50.2
unnamed: Q2.1 (G), R46.2, R48.1
unnamed: R45.1, R46.1, U21.4
unnamed: C58.1, U19.1 (CT)

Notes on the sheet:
SWITCHED CARRIER RAILS DISCHARGE
Local 3V3_AON feeds TPS22990 and the 1.8V LDO while EPS VBAT is on. Carrier permission gates both rails; inverter drives explicit rapid-discharge FETs. Module reset loss: 3.3V off within1.5ms,1.8V within4ms require actual load/ramp measurement.
